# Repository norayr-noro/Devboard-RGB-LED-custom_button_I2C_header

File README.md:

# THE MEOWBOARD™
For this project, I'll be designing the schematic and a custom PCB from that schematic based on the Stasis Devboard starter guide. The difference between mine and the guide's board is that mine adds an extra reset button, an LED for knowing if the PCB is on, and a custom RGB LED on the deboard itself (and don't forget the silkscreen art on the PCB!!)

And in the end, you will be able to build something like this (final PCB design):

(pico for comparison)

# 📖 Overview
In short, I'll be using the guide from Hack Club Stasis starter projects ( https://stasis.hackclub.com/starter-projects/devboard ) of which I'll be using the same RP2040 MCU chip, which is the same chip used in the rasberry pico and would act as the base of the whole devboard. By using this guide, I made my own basic devboard, which then I added an I2C header, an extra reset button, and more.

🛠️ Design & Components
In my design, I have used:
* 1** RP2040 - RP2040 - f.p. (Package_DFN_QFN:QFN-56-1EP_7x7mm_P0.4mm_EP3.2x3.2mm)
* 2** buttons - SW_Push - f.p (Button_Switch_SMD:SW_Push_SPST_NO_Alps_SKRK)
* 4** mounting holes - MountingHole (H) - f.p (MountingHole:MountingHole_2.2mm_M2)
* 1** USB-C receptacle - USB_C_Receptacle_2.0_14P - f.p (Connector_USB:USB_C_Receptacle_HRO_TYPE-C-31-M-12)
* 1** fixed voltage regulator - NCP1117-3.3_SOT223 - f.p (Package_TO_SOT_SMD:SOT-223-3_TabPin2)
* 1** SRAM (storage) - W25Q128JVS - (Package_SON:Winbond_USON-8-1EP_3x2mm_P0.5mm_EP0.2x1.6mm)
* 1** crystal oscillator - 12MHz crystal_GND24 - (Crystal:Crystal_SMD_3225-4Pin_3.2x2.5mm_HandSoldering)
* 1** I2C header pins 01x04 - Conn_01x04 - Connector_PinHeader_2.54mm:PinHeader_1x04_P2.54mm_Vertical
* 1** header pins 01x03 - Conn_01x03 - Connector_PinHeader_2.54mm:PinHeader_1x03_P2.54mm_Vertical
* 2** header pins 01*20 - Conn_01x20 - Connector_PinHeader_2.54mm:PinHeader_1x20_P2.54mm_Vertical
* 1** LED (on/off) - LED - LED_SMD:LED_0805_2012Metric_Pad1.15x1.40mm_HandSolder
* 1** RGB-LED - WS2812B - LED_SMD:LED_WS2812B_PLCC4_5.0x5.0mm_P3.2mm
* 2** 5.1K ohm resistors - R - Resistor_SMD:R_0402_1005Metric_Pad0.72x0.64mm_HandSolder
* 2** 27 ohm resistors - R - Resistor_SMD:R_0402_1005Metric_Pad0.72x0.64mm_HandSolder
* 3** 1K ohm resistors - R - Resistor_SMD:R_0402_1005Metric_Pad0.72x0.64mm_HandSolder
* 2** 10K ohm resistors - R - Resistor_SMD:R_0402_1005Metric_Pad0.72x0.64mm_HandSolder
* 2** 4.7K ohm resistors - R - Resistor_SMD:R_0402_1005Metric_Pad0.72x0.64mm_HandSolder
* 1** 330 resitor - R - Resistor_SMD:R_0402_1005Metric_Pad0.72x0.64mm_HandSolder
* 11* 0.1 uF capacitors - C - Capacitor_SMD:C_0402_1005Metric_Pad0.74x0.62mm_HandSolder
* 4** 1 uF capacitor - C - Capacitor_SMD:C_0402_1005Metric_Pad0.74x0.62mm_HandSolder
* 2** 15 pF capacitors - C -  Capacitor_SMD:C_0402_1005Metric_Pad0.74x0.62mm_HandSolder
  
And for designing the PCB, I used KiCad.

# ⚙️ Tools & Process
Using the base guide on stasis, I made a template schematic for my devboard. After which I added my own things to the devboard including:
* reset button using the run pin to GND
* I2C pin header using 3v3, GND, and GPIO pins 4 and 5, and 2 pull-up resistors connected to the 3v3 to the GPIO pins
* LED for knowing if the PCB is powered or off
* a customisable RGB LED, and the on i used is WS2812B
After adding all of that, the ending schematic looked like this:

# 📈 Progress
After this, the project went into the PCB stage. This was quite difficult at first, trying to cram all of this into such a small profile, so the prototype model of the PCB did not look that great. Knowing this would not be a sufficent for submition i did a complete re-work of the PCB and learnt a few things doing it, like the data wires from the USB-C should be around equal, or that the storage decoupling capacitors and the crystal oscillator should be really close to not cause errors in their own cases.
Another big think i learnt is how to check for errors and at the same time learnt how to make custom silkscreen art from images using the image converter on KiCad. Simply put, you import the image into the converter, slide the black/white indicator slider to your liking, and then use the negative or not, which suits best. After that, you export the footprint as silkscreen, then add that footprint to the pcb maker on KiCad, after which you could use the silkscreen footprint to your liking (i put my silkscreen and the reference images in the photos folder in this repository dont ask why its all cats i just though its might be funny and cool) after all of that the pcb looks something like this:

And also here's the final 3d model (back and front):

# Ordering 
For ordering this pcb i though that JLCPCBs might be best due to their "comparatively" cheap assembly of PCBs. If you want to order this PCB for yourself, check the stasis guide for a full explanation here(https://stasis.hackclub.com/starter-projects/devboard), but in a nutshell, you'd need to put the .gerber file (it's the zip file for this repository, no need to extract it!) and the select the settings youd want then select the PCBA option and then when you start to check out it would want a BOM file (the excel file where all the BILL OF MATTERIALS are) and a position file where they should go, after all of that it should select "most" of the parts for you, then you could just select and approve which part goes for which. All of that and you're done!

# BOM 
Also, I'll be adding the BOM file showing roughly where you can get all the parts and which parts I have used in this project.
	Price valued per unit and total price PER BOARD				
| Item	 |   URL	         |  Price (per unit )	| Quantity needed	|Quantity to order (min on JLCPCB) |	Total |
| --------- | ----------------------------------------------------------| -------- | ------------- | ----------------------| ------------ |
|1uf caps |	https://jlcpcb.com/partdetail/53938-CL05A105KA5NQNC/C52923 |	0.0039	| 4 |	8 |	$0.01 |
|0.1uf (100nf) caps |	https://jlcpcb.com/partdetail/1877-CL05B104KO5NNNC/C1525 |	0.0013	| 11 |	22 |	$0.01 |
|8pf caps |	https://jlcpcb.com/partdetail/1930-0402CG8R0C500NT/C1578 |	0.0012 |	2 |	4 |	$0.01 |
|SK6812MINI-E (RGB-LED) |	https://jlcpcb.com/partdetail/OPSCOOptoelectronics-SK6812MINIE/C5149201 |	0.086 |	1 |	2 |	$0.17 |
|LED |	https://jlcpcb.com/partdetail/85425-NCD0805R1/C84256 |	0.0133 |	1  |	2 |	$0.03 |
|USB-C female surface mount |	https://jlcpcb.com/partdetail/Korean_HropartsElec-TYPE_C_31_M12/C165948	 | 0.1832 |	1  |	2  |	$0.37  |
|5.1K resistors |	https://jlcpcb.com/partdetail/26648-0402WGF5101TCE/C25905 |	0.0009 |	2  |	4 |	$0.01 |
|27 ohm resistors	| https://jlcpcb.com/partdetail/25843-0402WGF270JTCE/C25100 |	0.0008 |	2  |	4	|$0.01 |
|10K resistors |	https://jlcpcb.com/partdetail/26487-0402WGF1002TCE/C25744 |	0.0013 |	2  |	4  |	$0.01 |
|330 ohm resistors |	https://jlcpcb.com/partdetail/25847-0402WGF3300TCE/C25104 |	0.0011 |	1  |	2  |	$0.01 |
|1K resistors	 | https://jlcpcb.com/partdetail/12256-0402WGF1001TCE/C11702	 | 0.001 |	3 |	6 |	$0.01 |
|4.7K resistors |	https://jlcpcb.com/partdetail/26643-0402WGF4701TCE/C25900	 | 0.001 |	2 |	4 |	$0.01 |
|push buttons	 | https://jlcpcb.com/partdetail/XUNPU-TS_1088AR02016/C720477	 | 0.0555 |	2 |	4 |	$0.11 |
|RP2040 |	https://jlcpcb.com/partdetail/RaspberryPi-RP2040/C2040	           | 0.9764	| 1 |	2 |	$1.95 |
|AMS1117-3.3	 | https://jlcpcb.com/partdetail/Advanced_MonolithicSystems-AMS1117_33/C6186 |	0.2118 |	1 |	2 |	$0.42  |
|W25Q128JVSIQ	 |https://jlcpcb.com/partdetail/WinbondElec-W25Q128JVSIQ/C97521	 | 1.892 |	1 |	2 |	$3.78  |
|NX3225GA 12MHZ	  |https://jlcpcb.com/partdetail/NDK-NX3225GA_12MHZ_STD_CRG2/C481407 |	0.249 |	1 |	2 | $0.50  |

| N/A | price (USD) |
| -------------------- | ------ |
| Subtotal (only parts) | 	8.23 |
|Shipping and handling |	1.5	 |			
|PCB |	4	|			
|Total (without assembly fees) |	13.73	|			
|Total (with fees)	| 38.09 |
# Updates - Notes
After reviewing the files, I have changed quite a few things with the help of a reviewer. My first thing is that I added the .csv a nd .xlsx files of all the parts for the PCB. Secondly, I updated the silkscreen design to remove the dotted lines, as they might cause some manufacturing difficulties. Continuing with the updates, I changed the WS2812B to an SK6812MINI-E and routed it's vdd to 5V instead of 3V3 due to it being out of spec for both cases. Finally, I changed the SRAM for a cheaper version, the W25Q128JVSIQ TR to the W25Q128JVSIQ, which is bigger, but it was quite cheaper than the last model. Other than that, I checked for any errors, did some polishing, and got there to be 0 DRC errors in sight.

# 💭 Final Thoughts + Conclusion
Overall, this project was not as difficult as expected, so while learning how devboards mainly function and actually work, I had fun while doing it, which was the main part to actually understand how it works. And now I'll just be waiting till the MEOWBOARD^(tm) comes!!!

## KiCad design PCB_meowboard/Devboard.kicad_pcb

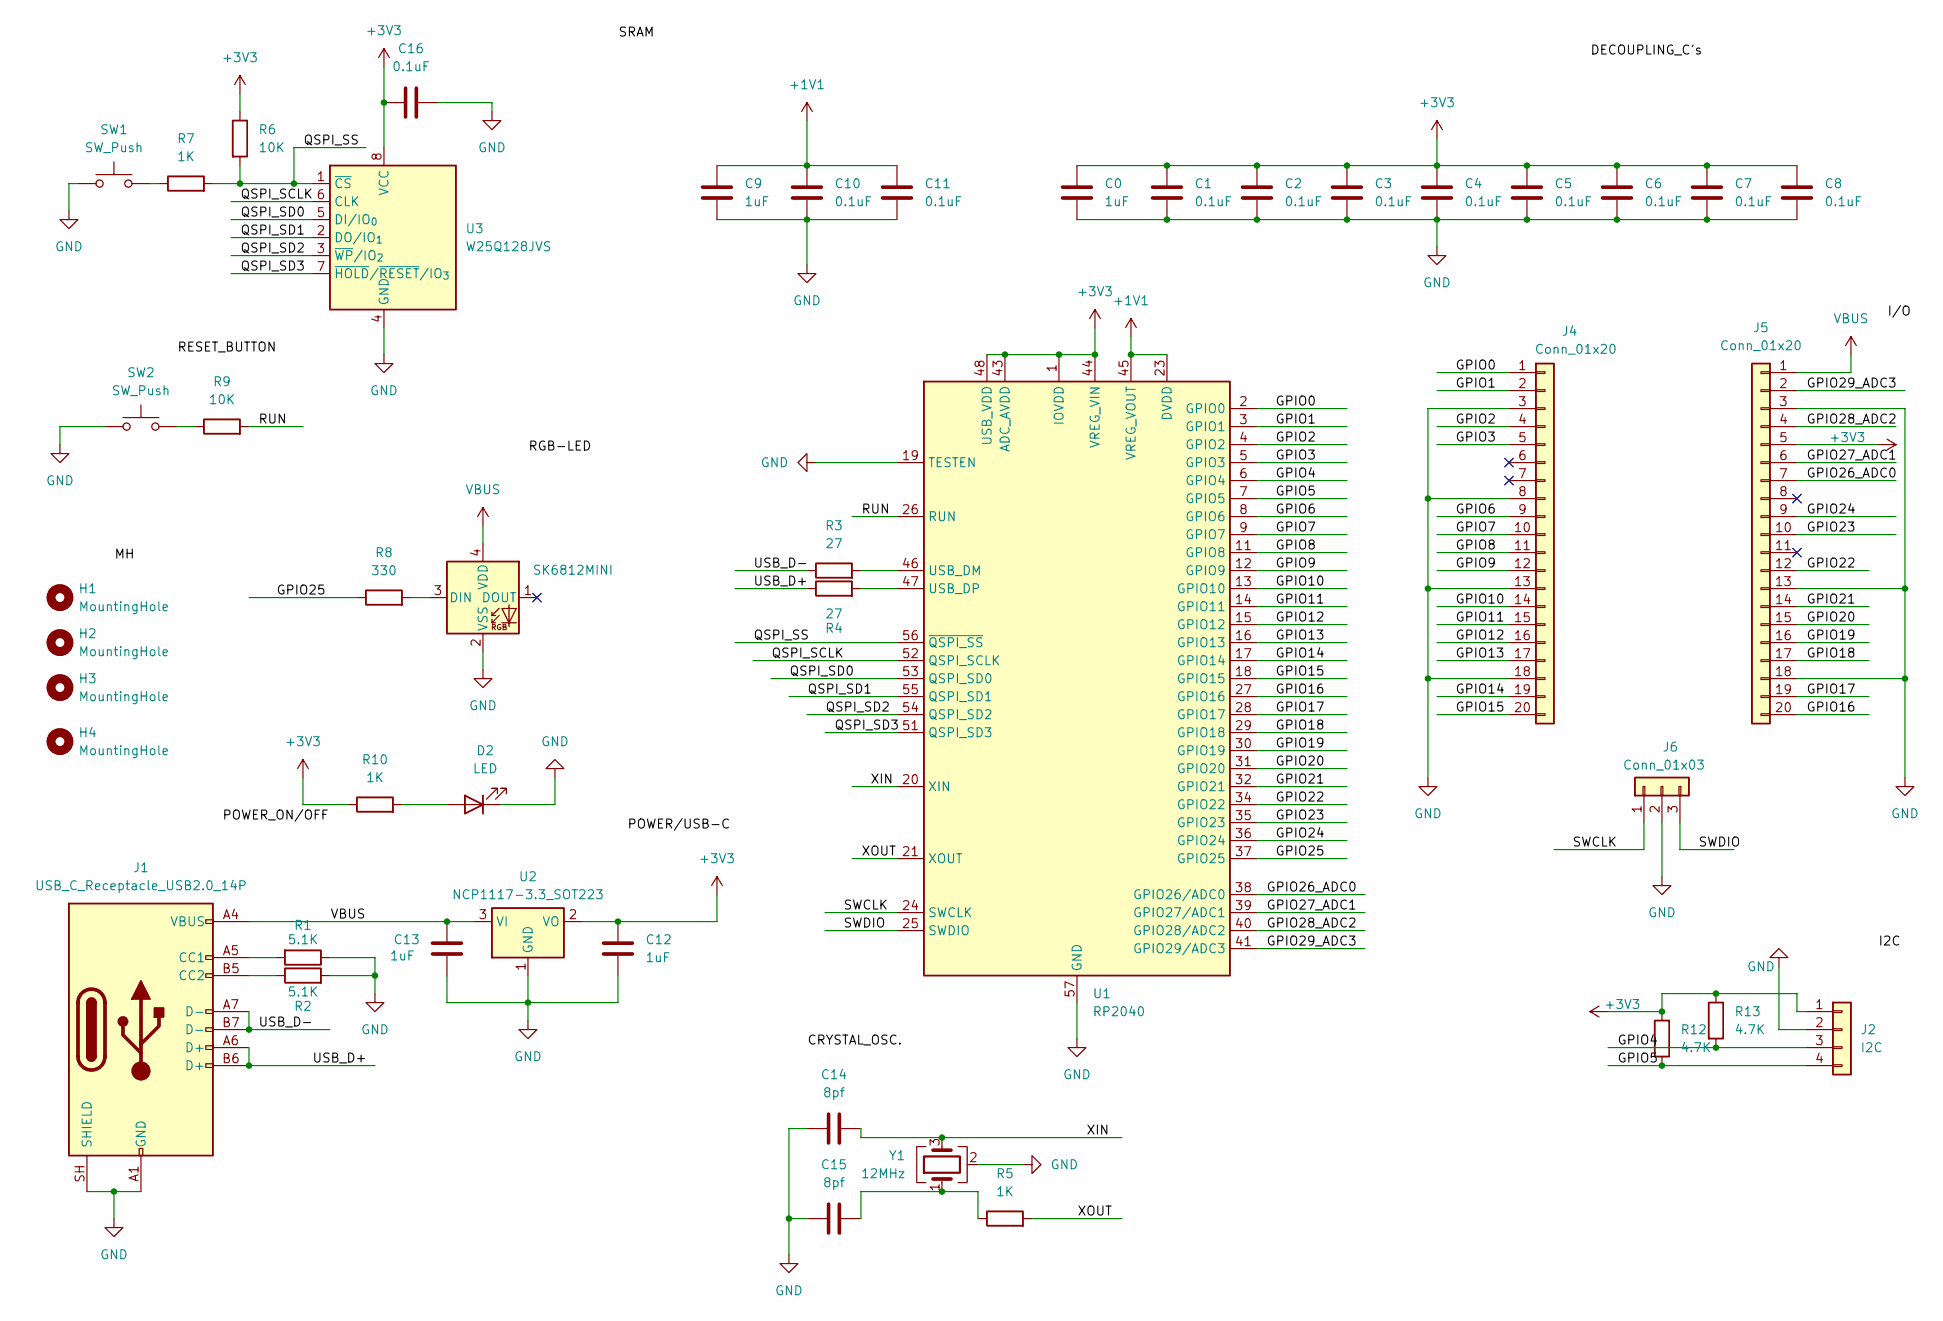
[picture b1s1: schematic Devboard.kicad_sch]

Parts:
C0, C9, C12, C13: 1uF; C_0402_1005Metric_Pad0.74x0.62mm_HandSolder
C1, C2, C3, C4, C5, C6, C7, C8, C10, C11, C16: 0.1uF; C_0402_1005Metric_Pad0.74x0.62mm_HandSolder
C14, C15: 8pf; C_0402_1005Metric_Pad0.74x0.62mm_HandSolder
D1: SK6812MINI; LED_SK6812MINI_PLCC4_3.5x3.5mm_P1.75mm
D2: LED; LED_0805_2012Metric_Pad1.15x1.40mm_HandSolder
H1, H2, H3, H4: MountingHole; MountingHole_2.2mm_M2
J1: USB_C_Receptacle_USB2.0_14P; USB_C_Receptacle_HRO_TYPE-C-31-M-12
J2: I2C; PinHeader_1x04_P2.54mm_Vertical
J4, J5: Conn_01x20; PinHeader_1x20_P2.54mm_Vertical
J6: Conn_01x03; PinHeader_1x03_P2.54mm_Vertical
R1, R2: 5.1K; R_0402_1005Metric_Pad0.72x0.64mm_HandSolder
R3, R4: 27; R_0402_1005Metric_Pad0.72x0.64mm_HandSolder
R5, R7, R10: 1K; R_0402_1005Metric_Pad0.72x0.64mm_HandSolder
R6, R9: 10K; R_0402_1005Metric_Pad0.72x0.64mm_HandSolder
R8: 330; R_0402_1005Metric_Pad0.72x0.64mm_HandSolder
R12, R13: 4.7K; R_0402_1005Metric_Pad0.72x0.64mm_HandSolder
SW1, SW2: SW_Push; SW_Push_SPST_NO_Alps_SKRK
U1: RP2040; QFN-56-1EP_7x7mm_P0.4mm_EP3.2x3.2mm
U2: NCP1117-3.3_SOT223; SOT-223-3_TabPin2
U3: W25Q128JVS; SOIC-8_5.3x5.3mm_P1.27mm
Y1: 12MHz; Crystal_SMD_3225-4Pin_3.2x2.5mm_HandSoldering

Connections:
+1V1: C9.1, C10.1, C11.1, U1.23 (DVDD), U1.45 (VREG_VOUT), U1.50 (DVDD)
+3V3: C0.1, C1.1, C2.1, C3.1, C4.1, C5.1, C6.1, C7.1, C8.1, C12.1, C16.1, J2.1, J5.5, R6.1, R10.1, R12.2, R13.1, U1.1 (IOVDD), U1.10 (IOVDD), U1.22 (IOVDD), U1.33 (IOVDD), U1.42 (IOVDD), U1.43 (ADC_AVDD), U1.44 (VREG_VIN), U1.48 (USB_VDD), U1.49 (IOVDD), U2.2 (VO), U3.8 (VCC)
/GPIO0: J4.1, U1.2 (GPIO0)
/GPIO1: J4.2, U1.3 (GPIO1)
/GPIO2: J4.4, U1.4 (GPIO2)
/GPIO3: J4.5, U1.5 (GPIO3)
/GPIO4: J2.3, R13.2, U1.6 (GPIO4)
/GPIO5: J2.4, R12.1, U1.7 (GPIO5)
/GPIO6: J4.9, U1.8 (GPIO6)
/GPIO7: J4.10, U1.9 (GPIO7)
/GPIO8: J4.11, U1.11 (GPIO8)
/GPIO9: J4.12, U1.12 (GPIO9)
/GPIO10: J4.14, U1.13 (GPIO10)
/GPIO11: J4.15, U1.14 (GPIO11)
/GPIO12: J4.16, U1.15 (GPIO12)
/GPIO13: J4.17, U1.16 (GPIO13)
/GPIO14: J4.19, U1.17 (GPIO14)
/GPIO15: J4.20, U1.18 (GPIO15)
/GPIO16: J5.20, U1.27 (GPIO16)
/GPIO17: J5.19, U1.28 (GPIO17)
/GPIO18: J5.17, U1.29 (GPIO18)
/GPIO19: J5.16, U1.30 (GPIO19)
/GPIO20: J5.15, U1.31 (GPIO20)
/GPIO21: J5.14, U1.32 (GPIO21)
/GPIO22: J5.12, U1.34 (GPIO22)
/GPIO23: J5.10, U1.35 (GPIO23)
/GPIO24: J5.9, U1.36 (GPIO24)
/GPIO25: R8.1, U1.37 (GPIO25)
/GPIO26_ADC0: J5.7, U1.38 (GPIO26/ADC0)
/GPIO27_ADC1: J5.6, U1.39 (GPIO27/ADC1)
/GPIO28_ADC2: J5.4, U1.40 (GPIO28/ADC2)
/GPIO29_ADC3: J5.2, U1.41 (GPIO29/ADC3)
/QSPI_SCLK: U1.52 (QSPI_SCLK), U3.6 (CLK)
/QSPI_SD0: U1.53 (QSPI_SD0), U3.5 (DI/IO_{0})
/QSPI_SD1: U1.55 (QSPI_SD1), U3.2 (DO/IO_{1})
/QSPI_SD2: U1.54 (QSPI_SD2), U3.3 (~WP/IO_{2})
/QSPI_SD3: U1.51 (QSPI_SD3), U3.7 (~HOLD/~RESET/IO_{3})
/QSPI_SS: R6.2, R7.2, U1.56 (~QSPI_SS), U3.1 (~CS)
/RUN: R9.2, U1.26 (RUN)
/SWCLK: J6.1, U1.24 (SWCLK)
/SWDIO: J6.3, U1.25 (SWDIO)
/USB_D+: J1.A6 (D+), J1.B6 (D+), R4.1
/USB_D-: J1.A7 (D-), J1.B7 (D-), R3.1
/XIN: C14.2, U1.20 (XIN), Y1.3
/XOUT: R5.2, U1.21 (XOUT)
GND: C0.2, C1.2, C2.2, C3.2, C4.2, C5.2, C6.2, C7.2, C8.2, C9.2, C10.2, C11.2, C12.2, C13.2, C14.1, C15.2, C16.2, D1.2 (VSS), D2.1 (K), J1.A1 (GND), J1.A12 (GND), J1.B1 (GND), J1.B12 (GND), J1.SH (SHIELD), J2.2, J4.3, J4.8, J4.13, J4.18, J5.3, J5.13, J5.18, J6.2, R1.1, R2.2, SW1.1, SW2.1, U1.19 (TESTEN), U1.57 (GND), U2.1 (GND), U3.4 (GND), Y1.2 (G), Y1.4 (G)
unnamed: C15.1, R5.1, Y1.1
unnamed: D1.3 (DIN), R8.2
unnamed: D2.2 (A), R10.2
unnamed: J1.A5 (CC1), R1.2
unnamed: J1.B5 (CC2), R2.1
unnamed: R7.1, SW1.2
unnamed: R9.1, SW2.2
unnamed: R3.2, U1.46 (USB_DM)
unnamed: R4.2, U1.47 (USB_DP)
VBUS: C13.1, D1.4 (VDD), J1.A4 (VBUS), J1.A9 (VBUS), J1.B4 (VBUS), J1.B9 (VBUS), J5.1, U2.3 (VI)

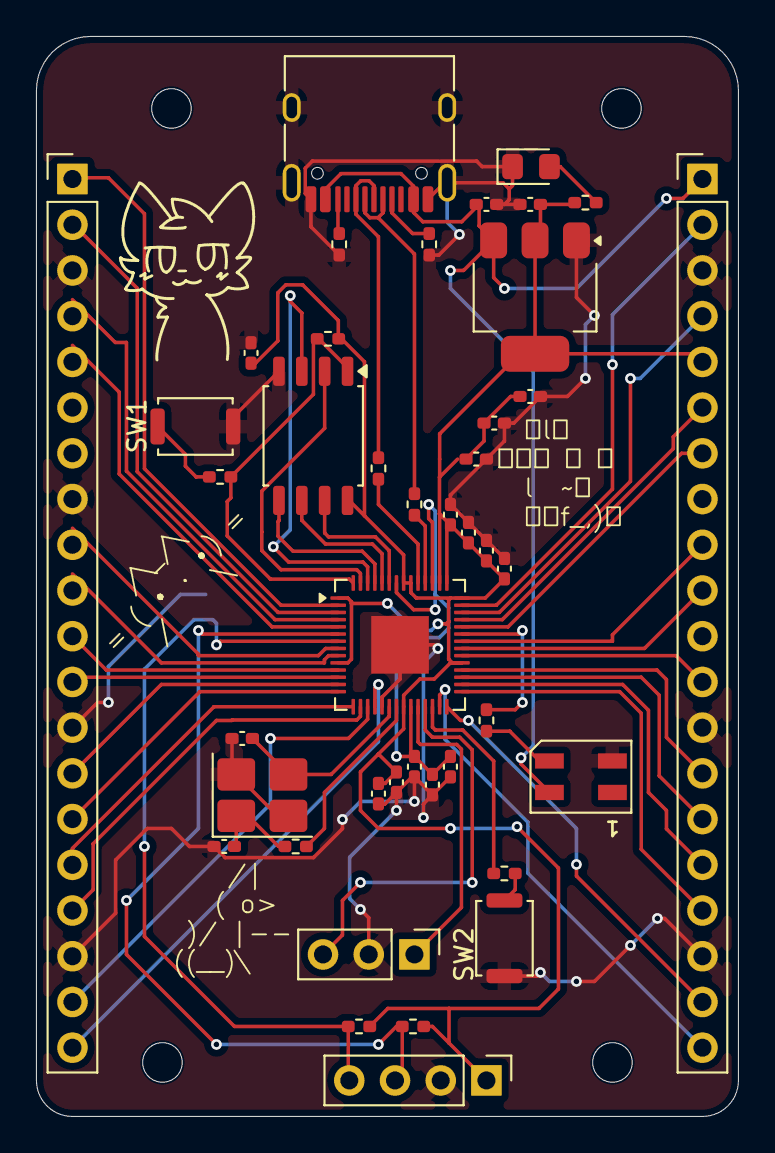
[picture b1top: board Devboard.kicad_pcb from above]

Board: 2 copper layers, 39.0 x 60.0 mm, 46 parts (0 on the bottom side), 56 nets.

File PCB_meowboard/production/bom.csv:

Designator,Footprint,Quantity,Value,LCSC Part #
"C0, C12, C13, C9",0402,4,1uF,
"C1, C10, C11, C16, C2, C3, C4, C5, C6, C7, C8",0402,11,0.1uF,
"C14, C15",0402,2,8pf,
D1,LED_SK6812MINI_PLCC4_3.5x3.5mm_P1.75mm,1,SK6812MINI,
D2,0805,1,LED,
J1,USB_C_Receptacle_HRO_TYPE-C-31-M-12,1,USB_C_Receptacle_USB2.0_14P,
J2,PinHeader_1x04_P2.54mm_Vertical,1,I2C,
"J4, J5",PinHeader_1x20_P2.54mm_Vertical,2,Conn_01x20,
J6,PinHeader_1x03_P2.54mm_Vertical,1,Conn_01x03,
"R1, R2",0402,2,5.1K,
"R10, R5, R7",0402,3,1K,
"R12, R13",0402,2,4.7K,
"R3, R4",0402,2,27,
"R6, R9",0402,2,10K,
R8,0402,1,330,
"SW1, SW2",SW_Push_SPST_NO_Alps_SKRK,2,SW_Push,
U1,QFN-56-1EP_7x7mm_P0.4mm_EP3.2x3.2mm,1,RP2040,
U2,SOT-223-3_TabPin2,1,NCP1117-3.3_SOT223,
U3,SOIC-8_5.3x5.3mm_P1.27mm,1,W25Q128JVS,
Y1,Crystal_SMD_3225-4Pin_3.2x2.5mm_HandSoldering,1,12MHz,

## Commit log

2026-05-01 Revise README for THE MEOWBOARD™ project
    Updated project name and description to reflect new features and design.
2026-05-03 Enhance README with project details and instructions
    Expanded the README to include detailed project overview, design components, tools used, progress updates, ordering instructions, and final thoughts.
2026-05-06 Made all the required reworks
    make the pcb with 0 drc errors and warnings changed the silkscreen to fit and be able to be manufatured (basically made it an outline) changed the SRAM module due toe the bigger same type being quite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
2026-05-06 Fix grammar and formatting in README.md
    Corrected grammar, punctuation, and formatting issues throughout the README. Updated component descriptions and project details for clarity.
2026-05-06 Enhance README with PCB details and images
    Updated PCB section with images and ordering information.
2026-05-06 Fix formatting and update PCB changes in README
    Corrected section headers and updated notes on PCB changes, including part substitutions and design modifications.
2026-05-15 Add BOM section and update ordering instructions
    Added BOM section with part details and pricing for PCB assembly.
2026-05-15 Revise parts list and update total costs
    Updated parts list and total costs in README.md.
2026-06-18 Enhance README with final PCB design images
    Added images and additional details about the final PCB design.
2026-06-26 Update README.md
    updated full assembly photos
